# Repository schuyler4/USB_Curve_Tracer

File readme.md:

<h2> USB Curve Tracer </h2>
This is my attempt at making a curve tracer.  
Instead of implementing a display, data is piped to an external computer where it is plotted using Python. It is also controlled using a command line interface on the external computer. 

<h3> Revision 3 Specs </h3>
<ul>
<li>12V External Power Supply</li>
<li>Maximum Positive Sweep Voltage: 4V</li>
<li>Minimum Negative Sweep Voltage: -3.9V</li>
<li>Full Sweep Time: 15.4s</li>
</ul>

<h3> Limitations </h3>
<ul>
<li>The curve tracer does not use sinusoidal waveforms for measurement; measuring reactive components 
(Capacitors and Inductors) probably will not work. </li>
<li>The curve tracer cannot be driven, so it cannot measure voltage sources.</li>
<li>The curve tracer does not include Kelvin connection functionality, so test lead resistance and 
contact resistance will be included in the measurement. </li>
<li> The curve tracer does not include any programmable gain stages. For this reason, you only get full
current/voltage measurement when using the full current/voltage range.</li>
</ul> 

<h3> Examples </h3>
<p>Below is an example 1N4148 diode sweep and a 2N3904 BJT sweep. Short of curve tracing with a different system and doing a comparison, there is not really a good way to verify if these are correct. However, the general shape of the curves does look right. There is clearly some offset error for the red trace of the 2N3904 sweep. </p>

<h3> Schematic </h3>

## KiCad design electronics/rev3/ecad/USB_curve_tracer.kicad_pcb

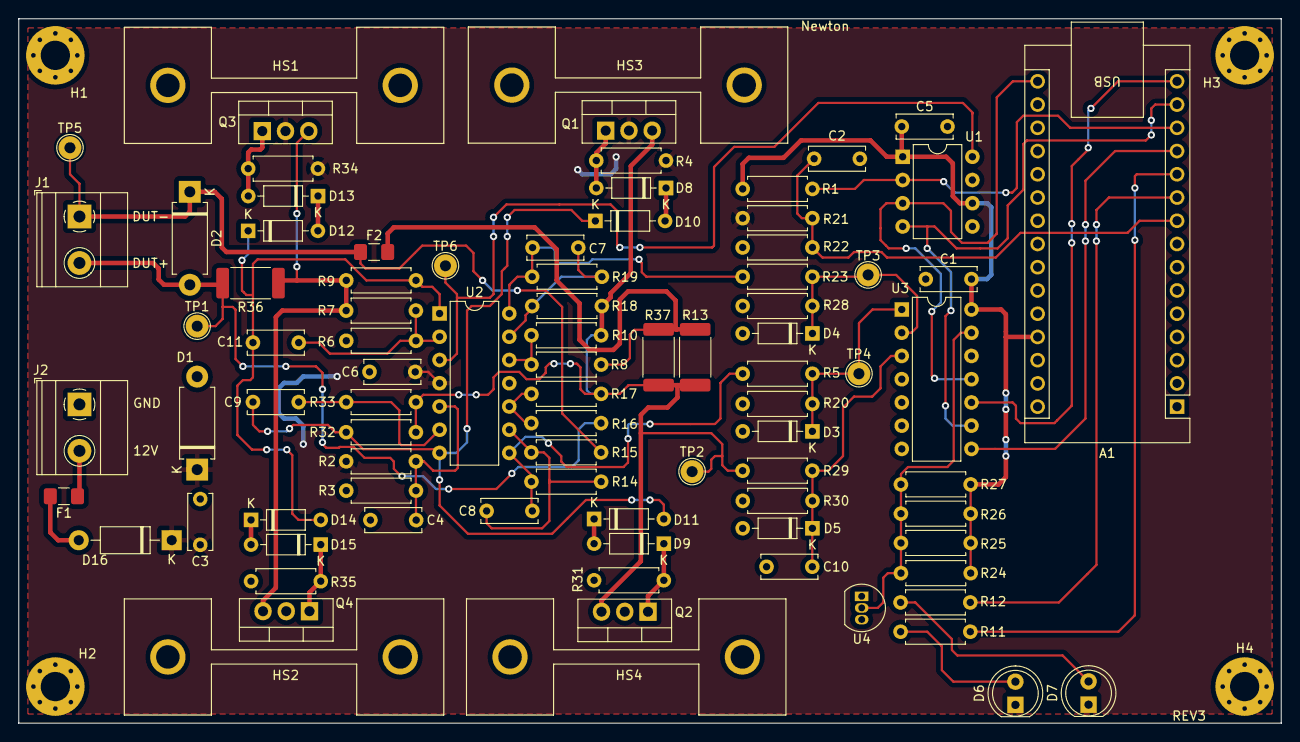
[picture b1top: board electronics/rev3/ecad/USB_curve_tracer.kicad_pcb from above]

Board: 2 copper layers, 138.0 x 77.0 mm, 91 parts (0 on the bottom side), 44 nets.

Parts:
A1: Arduino_Nano_v3.x; Arduino_Nano
C1, C2, C4, C5, C6, C10: 0.1uF; C_Disc_D6.0mm_W2.5mm_P5.00mm
C3: 10uF; C_Disc_D6.0mm_W2.5mm_P5.00mm
C7, C8: 10nF; C_Disc_D6.0mm_W2.5mm_P5.00mm
C9, C11: 100pF; C_Disc_D6.0mm_W2.5mm_P5.00mm
D1: SA13A; D_DO-15_P10.16mm_Horizontal
D2: SA13CA; D_DO-15_P10.16mm_Horizontal
D3, D4, D5: BZX79-C2V4; D_DO-35_SOD27_P7.62mm_Horizontal
D6: WP7113SGD; LED_D5.0mm
D7: WP7113ID; LED_D5.0mm
D8, D9, D10, D11, D12, D13, D14, D15: 1N4148; D_DO-35_SOD27_P7.62mm_Horizontal
D16: 1N5817; D_DO-41_SOD81_P10.16mm_Horizontal
F1: 3A; Fuse_1206_3216Metric_Pad1.42x1.75mm_HandSolder
F2: 1A; Fuse_1206_3216Metric_Pad1.42x1.75mm_HandSolder
H1, H2, H3, H4: M3; MountingHole_3.2mm_M3_Pad_Via
HS1, HS2, HS3, HS4: 13.40°C/W; HSINK_531002B02500G
J1: DUT Connector; TerminalBlock_Phoenix_MKDS-1,5-2-5.08_1x02_P5.08mm_Horizont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
J2: Power Input; TerminalBlock_Phoenix_MKDS-1,5-2-5.08_1x02_P5.08mm_Horizont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
Q1, Q3: TIP122; TO-220-3_Vertical
Q2, Q4: TIP127; TO-220-3_Vertical
R1, R2, R3, R6, R7, R22, R24, R25, R26, R27, R33: 10k; R_Axial_DIN0207_L6.3mm_D2.5mm_P7.62mm_Horizontal
R4, R31, R34, R35: 4.7k; R_Axial_DIN0207_L6.3mm_D2.5mm_P7.62mm_Horizontal
R5, R23, R29: 3.83k+/-0.1%; R_Axial_DIN0207_L6.3mm_D2.5mm_P7.62mm_Horizontal
R8, R18, R20, R28: 1k+/-0.1%; R_Axial_DIN0207_L6.3mm_D2.5mm_P7.62mm_Horizontal
R9, R30, R32: 1k; R_Axial_DIN0207_L6.3mm_D2.5mm_P7.62mm_Horizontal
R10, R19: 11.8k+/-0.1%; R_Axial_DIN0207_L6.3mm_D2.5mm_P7.62mm_Horizontal
R11, R12: 619; R_Axial_DIN0207_L6.3mm_D2.5mm_P7.62mm_Horizontal
R13, R37: 1+/-1%; R_2512_6332Metric_Pad1.40x3.35mm_HandSolder
R14, R15, R16, R17: 10k+/-0.1%; R_Axial_DIN0207_L6.3mm_D2.5mm_P7.62mm_Horizontal
R21: 14k; R_Axial_DIN0207_L6.3mm_D2.5mm_P7.62mm_Horizontal
R36: 1.5; R_2512_6332Metric_Pad1.40x3.35mm_HandSolder
TP1, TP2, TP3, TP4, TP5, TP6: 4952; TestPoint_THTPad_D2.5mm_Drill1.2mm
U1: MCP4911; DIP-8_W7.62mm
U2: LMC6484A; DIP-14_W7.62mm
U3: MCP3204; DIP-14_W7.62mm
U4: LM385BZ-2.5; TO-92_Inline

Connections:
+5V: A1.27 (+5V), C1.1, C5.1, R1.1, R24.1, R25.1, R26.1, R27.1, U1.1 (Vdd), U1.6 (Vref), U3.14 (Vdd)
+12V: C3.1, C6.1, D1.1 (K), D16.1 (K), Q1.2 (C), Q3.2 (C), R2.1, R4.1, R21.1, R34.1, U2.4 (V+)
/IV_Variation/DUT_I: D4.1 (K), R23.2, R28.1, TP3.1, U3.2 (CH1)
/IV_Variation/DUT_V: D3.1 (K), R5.2, R20.1, TP4.1, U3.1 (CH0)
/IV_Variation/Sweep Voltage Buffer/Sweep_Amplified: Q3.3 (E), Q4.3 (E), R7.2, R9.2, R36.1
/IV_Variation/Sweep_Input: TP6.1, U1.8 (Vout), U2.3 (+)
/IV_Variation/Vmiddle: C10.1, D5.1 (K), R29.2, R30.1, U3.3 (CH2)
GND: A1.4 (GND), A1.29 (GND), C1.2, C2.2, C3.2, C4.2, C5.2, C6.2, C10.2, D1.2 (A), D3.2 (A), D4.2 (A), D5.2 (A), D6.1 (K), D7.1 (K), H1.1, H2.1, H3.1, H4.1, J2.1, Q2.2 (C), Q4.2 (C), R3.2, R6.2, R20.2, R22.2, R28.2, R30.2, R31.2, R35.2, U1.5 (~LDAC), U1.7 (Vss), U2.11 (V-), U3.7 (DGND), U3.12 (AGND), U4.3 (A)
unnamed: A1.9 (D6), C2.1, R21.2, R22.1
unnamed: A1.10 (D7), R12.2
unnamed: A1.11 (D8), R11.2
unnamed: A1.12 (D9), U3.8 (~CS/SHDN)
unnamed: A1.13 (D10), R1.2, U1.2 (~CS)
unnamed: A1.14 (D11), U1.4 (SDI), U3.9 (Din)
unnamed: A1.15 (D12), U3.10 (Dout)
unnamed: A1.16 (D13), U1.3 (SCK), U3.11 (CLK)
unnamed: C7.2, R19.2, R23.1, U2.14
unnamed: C8.2, R5.1, R14.2, U2.8
unnamed: D2.1 (A1), F2.1, J1.1, R15.1, TP5.1
unnamed: D2.2 (A2), J1.2, R16.1, R36.2, TP1.1
unnamed: D6.2 (A), R11.1
unnamed: D7.2 (A), R12.1
unnamed: D8.2 (A), Q1.1 (B), R4.2
unnamed: D9.1 (K), Q2.1 (B), R31.1
unnamed: D8.1 (K), D10.2 (A)
unnamed: C9.2, D10.1 (K), D11.2 (A), R32.1, U2.7
unnamed: D9.2 (A), D11.1 (K)
unnamed: D12.2 (A), D13.1 (K)
unnamed: C11.1, D12.1 (K), D14.2 (A), R9.1, U2.1
unnamed: D13.2 (A), Q3.1 (B), R34.2
unnamed: D14.1 (K), D15.2 (A)
unnamed: D15.1 (K), Q4.1 (B), R35.1
unnamed: D16.2 (A), F1.2
unnamed: F2.2, R8.1, R13.1, R37.1
unnamed: F1.1, J2.2
unnamed: C11.2, R6.1, R7.1, U2.2 (-)
unnamed: C4.1, R2.2, R3.1, U2.5 (+)
unnamed: C9.1, R33.1, U2.6 (-)
unnamed: R16.2, R17.1, U2.10 (+)
unnamed: C8.1, R14.1, R15.2, U2.9 (-)
unnamed: R8.2, R10.1, U2.12 (+)
unnamed: C7.1, R18.2, R19.1, U2.13 (-)
unnamed: R24.2, R25.2, R26.2, R27.2, U3.13 (Vref), U4.2 (K)
V/2: Q1.3 (E), Q2.3 (E), R10.2, R13.2, R17.2, R18.1, R29.1, R32.2, R33.2, R37.2, TP2.1

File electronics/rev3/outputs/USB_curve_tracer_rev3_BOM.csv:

Item,Qty,Reference(s),Value,Distributor Part #,Part #,Unit Price,Price
1,1,A1,Arduino_Nano_v3.x,1050-ABX00033-ND,ABX00033,14.91,14.91
2,6,"C1, C2, C4, C5, C6, C10",0.1uF,BC2665CT-ND,K104K10X7RF5UH5,0.23,1.38
3,1,C3,10uF,445-173437-1-ND,FG26X7R1E106KRT06,0.65,0.65
4,2,"C7, C8",10nF,BC2662CT-ND,K103K10X7RF5UH5,0.22,0.44
5,2,"C9, C11",100pF,56-K101J10C0GF5UH5CT-ND,K101J10C0GF5UH5,0.23,0.46
6,1,D1,SA13A,SA13A-E3/54GICT-ND,SA13A-E3/54,0.46,0.46
7,1,D2,SA13CA,SA13CACT-ND,SA13CA,0.49,0.49
8,3,"D3, D4, D5",BZX79-C2V4,1727-2115-1-ND,"BZX79-C2V4,113",0.16,0.48
9,1,D6,WP7113SGD,754-1735-ND,WP7113SGD,0.34,0.34
10,1,D7,WP7113ID,754-1264-ND,WP7113ID,0.1,0.1
11,8,"D8, D9, D10, D11, D12, D13, D14, D15",1N4148,1N4148FS-ND,1N4148,0.1,0.8
12,1,D16,1N5817,497-4547-1-ND,1N5817,0.44,0.44
13,1,F1,3A,507-1896-1-ND,0685T3000-01,0.32,0.32
14,1,F2,1A,507-1077-1-ND,C1Q 1,0.33,0.33
15,4,"HS1, HS2, HS3, HS4",13.40°C/W,HS351-ND,531002B02500G,1.55,6.2
16,1,J1,DUT Connector,102-6179-ND,TB004-508-02BE,0.71,0.71
17,1,J2,Power Input,102-6179-ND,TB004-508-02BE,0.71,0.71
18,2,"Q1, Q3",TIP122,TIP122GOS-ND,TIP122G,0.79,1.58
19,2,"Q2, Q4",TIP127,TIP127GOS-ND,TIP127G,1.37,2.74
20,11,"R1, R2, R3, R6, R7, R22, R24, R25, R26, R27, R33",10k,CF14JT10K0CT-ND,CF14JT10K0,0.1,1.1
21,4,"R4, R31, R34, R35",4.7k,CF14JT4K70CT-ND,CF14JT4K70,0.1,0.4
22,3,"R5, R23, R29",4.02k+/-0.1%,1712-YR1B4K02CT-ND,YR1B4K02,0.63,1.89
23,4,"R8, R18, R20, R28",1k+/-0.1%,A105942CT-ND,YR1B1K0CC,0.63,2.52
24,3,"R9, R30, R32",1k,13-MFR-25FRF52-1KCT-ND,MFR-25FRF52-1K,0.1,0.3
25,2,"R10, R19",11.8k+/-0.1%,1712-YR1B11K8CCCT-ND,YR1B11K8CC,0.63,1.26
26,2,"R11, R12",619,619XBK-ND,MFR-25FBF52-619R,0.1,0.2
27,2,"R13, R37",1+/-1%,RMCF2512FT1R00CT-ND,RMCF2512FT1R00,0.27,0.54
28,4,"R14, R15, R16, R17",10k+/-0.1%,A105970CT-ND,YR1B10KCC,0.63,2.52
29,1,R21,14k,14.0KXBK-ND,MFR-25FBF52-14K,0.1,0.1
30,1,R36,1.5,A121179CT-ND,35221R5JT,1.22,1.22
31,6,"TP1, TP2, TP3, TP4, TP5, TP6",4952,36-4952-ND,4952,0.26,1.56
32,1,U1,MCP4911,MCP4911-E/P-ND,MCP4911-E/P,1.97,1.97
33,1,U2,LMC6484A,LMC6484IN/NOPB-ND,LMC6484IN/NOPB,2.83,2.83
34,1,U3,MCP3204,MCP3204-CI/P-ND,MCP3204-CI/P,4.52,4.52
35,1,U4,LM385BZ-2.5,LM385BZ-2.5GOS-ND,LM385BZ-2.5G,0.78,0.78
,,,,,,,57.25

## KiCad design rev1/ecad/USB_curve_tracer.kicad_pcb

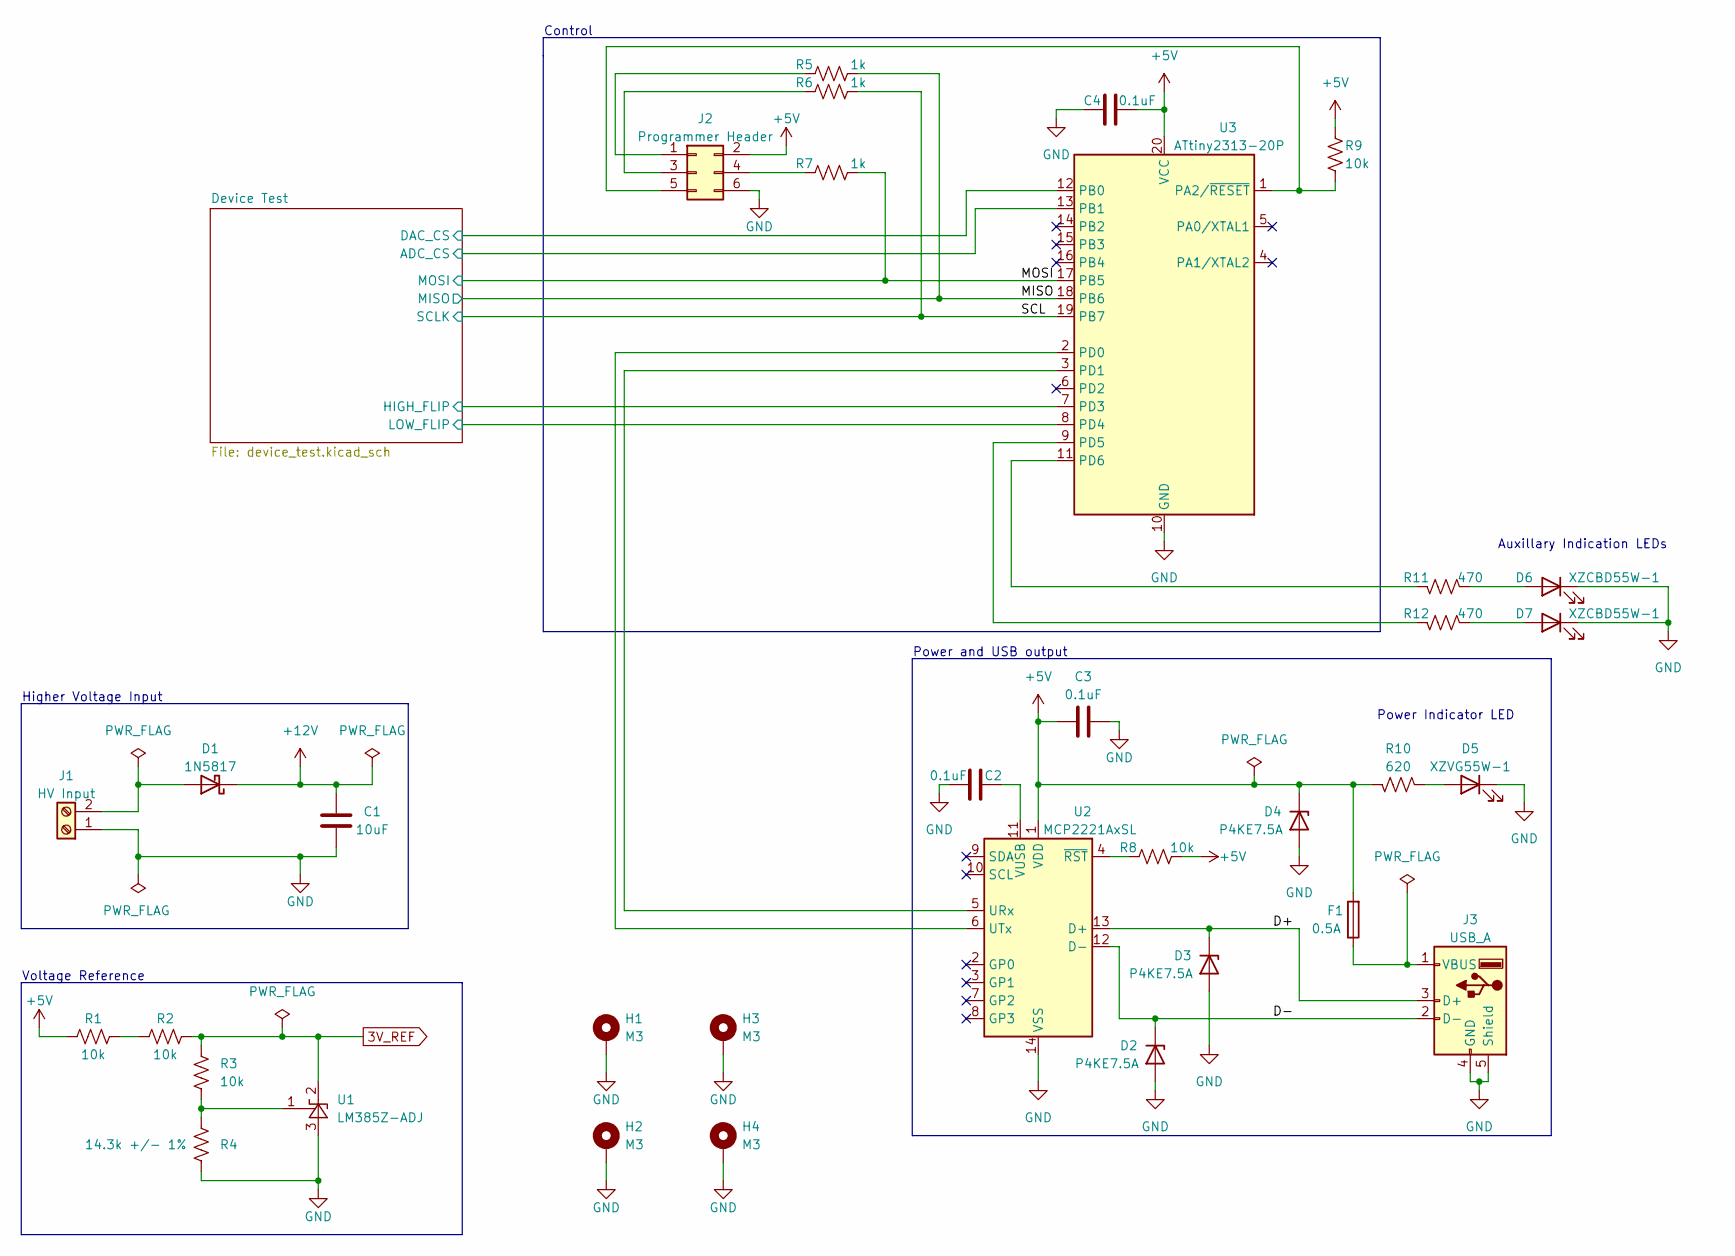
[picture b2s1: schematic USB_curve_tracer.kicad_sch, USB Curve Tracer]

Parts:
C1: 10uF; C_Disc_D6.0mm_W2.5mm_P5.00mm
C2, C3, C4: 0.1uF; C_Disc_D6.0mm_W2.5mm_P5.00mm
D1: 1N5817; D_DO-41_SOD81_P10.16mm_Horizontal
D2, D3, D4: P4KE7.5A; D_DO-41_SOD81_P7.62mm_Horizontal
D5: XZVG55W-1; LED_1206_3216Metric_Pad1.42x1.75mm_HandSolder
D6, D7: XZCBD55W-1; LED_1206_3216Metric_Pad1.42x1.75mm_HandSolder
F1: 0.5A; Fuse_1206_3216Metric_Pad1.42x1.75mm_HandSolder
H1, H2, H3, H4: M3; MountingHole_3.2mm_M3_Pad_Via
J1: HV Input; TerminalBlock_Phoenix_MKDS-1,5-2-5.08_1x02_P5.08mm_Horizont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
J2: Programmer Header; PinSocket_2x03_P2.54mm_Vertical
J3: USB_A; USB_B_OST_USB-B1HSxx_Horizontal
R1, R2, R3, R8, R9: 10k; R_Axial_DIN0207_L6.3mm_D2.5mm_P7.62mm_Horizontal
R4: 14.3k +/- 1%; R_Axial_DIN0207_L6.3mm_D2.5mm_P7.62mm_Horizontal
R5, R6, R7: 1k; R_Axial_DIN0207_L6.3mm_D2.5mm_P7.62mm_Horizontal
R10: 620; R_Axial_DIN0207_L6.3mm_D2.5mm_P7.62mm_Horizontal
R11, R12: 470; R_Axial_DIN0207_L6.3mm_D2.5mm_P7.62mm_Horizontal
U1: LM385Z-ADJ; TO-92_Inline
U2: MCP2221AxSL; SOIC-14_3.9x8.7mm_P1.27mm
U3: ATtiny2313-20P; DIP-20_W7.62mm

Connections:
3V_REF: R2.2, R3.1, U1.2 (K); also elsewhere on the board
+5V: C3.2, C4.2, D4.1 (K), F1.2, J2.2, R1.1, R8.2, R9.1, R10.2, U2.1 (VDD), U3.20 (VCC); also elsewhere on the board
+12V: C1.2, D1.1 (K); also elsewhere on the board
/D+: D3.1 (K), J3.3 (D+), U2.13 (D+)
/D-: D2.1 (K), J3.2 (D-), U2.12 (D-)
/Device Test/ADC_CS: U3.13 (PB1); also elsewhere on the board
/Device Test/DAC_CS: U3.12 (PB0); also elsewhere on the board
/Device Test/HIGH_FLIP: U3.7 (PD3); also elsewhere on the board
/Device Test/LOW_FLIP: U3.8 (PD4); also elsewhere on the board
/MISO: R5.2, U3.18 (PB6); also elsewhere on the board
/MOSI: R7.2, U3.17 (PB5); also elsewhere on the board
/SCL: R6.2, U3.19 (PB7); also elsewhere on the board
GND: C1.1, C2.2, C3.1, C4.1, D2.2 (A), D3.2 (A), D4.2 (A), D5.1 (K), D6.1 (K), D7.1 (K), H1.1, H2.1, H3.1, H4.1, J1.1, J2.6, J3.4 (GND), J3.5 (Shield), R4.2, U1.3 (A), U2.14 (VSS), U3.10 (GND); also elsewhere on the board
unnamed: C2.1, U2.11 (VUSB)
unnamed: D1.2 (A), J1.2
unnamed: D5.2 (A), R10.1
unnamed: D6.2 (A), R11.1
unnamed: D7.2 (A), R12.1
unnamed: F1.1, J3.1 (VBUS)
unnamed: J2.1, R5.1
unnamed: J2.3, R6.1
unnamed: J2.4, R7.1
unnamed: J2.5, R9.2, U3.1 (PA2/~RESET)
unnamed: R1.2, R2.1
unnamed: R3.2, R4.1, U1.1 (FB)
unnamed: R8.1, U2.4 (~RST)
unnamed: R11.2, U3.11 (PD6)
unnamed: R12.2, U3.9 (PD5)
unnamed: U2.5 (URx), U3.3 (PD1)
unnamed: U2.6 (UTx), U3.2 (PD0)

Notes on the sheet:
Power Indicator LED
Voltage Reference
Control
Power and USB output
Higher Voltage Input
Auxillary Indication LEDs

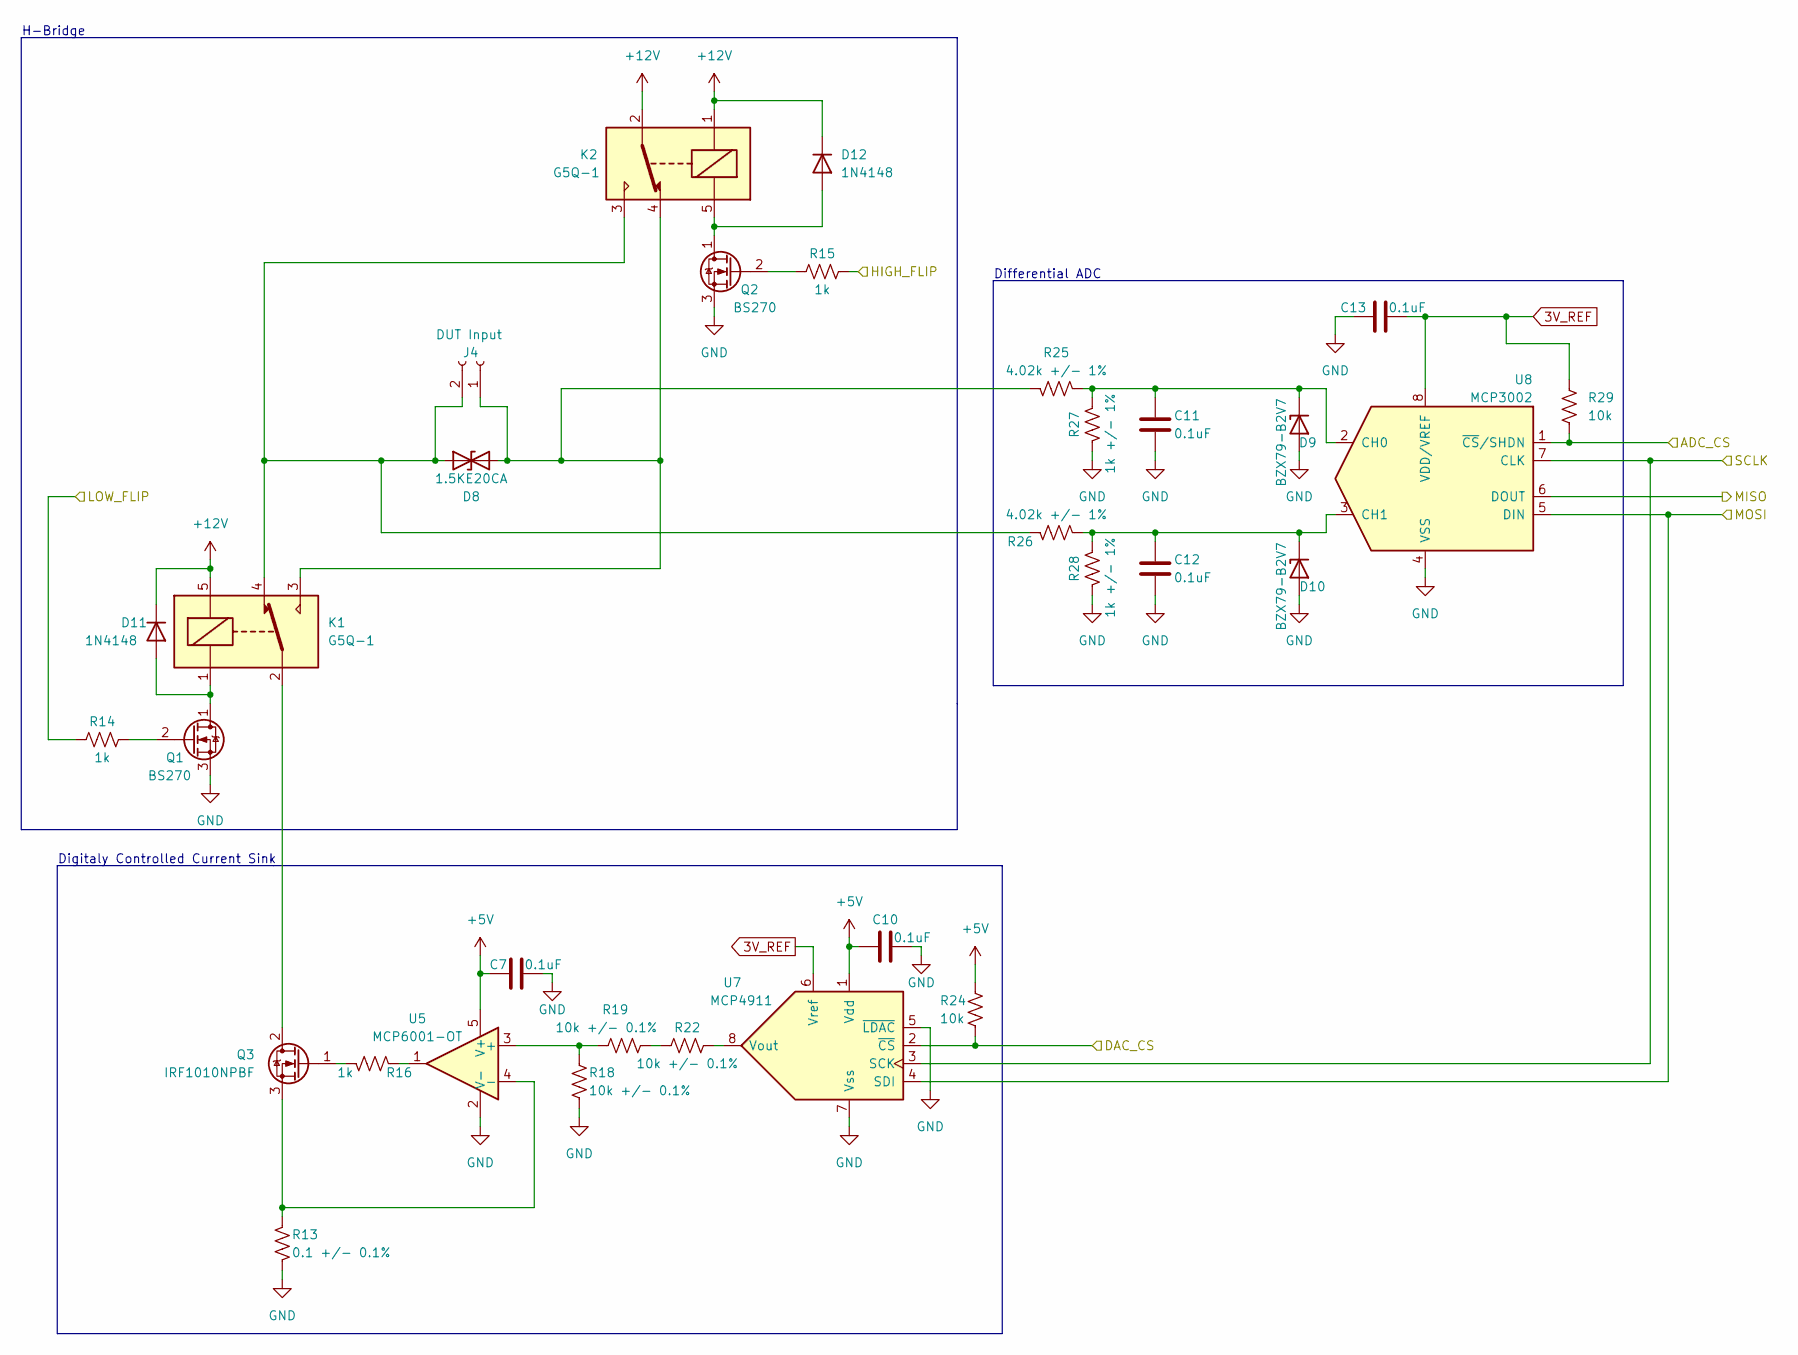
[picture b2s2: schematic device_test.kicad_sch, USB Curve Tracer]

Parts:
C7, C10, C11, C12, C13: 0.1uF; C_Disc_D6.0mm_W2.5mm_P5.00mm
D8: 1.5KE20CA; D_SMA_Handsoldering
D9, D10: BZX79-B2V7; D_DO-41_SOD81_P7.62mm_Horizontal
D11, D12: 1N4148; D_DO-35_SOD27_P7.62mm_Horizontal
J4: DUT Input; PinSocket_1x02_P2.54mm_Vertical
K1, K2: G5Q-1; Relay_SPDT_Omron-G5Q-1
Q1, Q2: BS270; TO-92_Inline
Q3: IRF1010NPBF; TO-220-3_Vertical
R13: 0.1 +/- 0.1%; R_Axial_DIN0207_L6.3mm_D2.5mm_P7.62mm_Horizontal
R14, R15, R16: 1k; R_Axial_DIN0207_L6.3mm_D2.5mm_P7.62mm_Horizontal
R18, R19, R22: 10k +/- 0.1%; R_Axial_DIN0207_L6.3mm_D2.5mm_P7.62mm_Horizontal
R24, R29: 10k; R_Axial_DIN0207_L6.3mm_D2.5mm_P7.62mm_Horizontal
R25, R26: 4.02k +/- 1%; R_Axial_DIN0207_L6.3mm_D2.5mm_P7.62mm_Horizontal
R27, R28: 1k +/- 1%; R_Axial_DIN0207_L6.3mm_D2.5mm_P7.62mm_Horizontal
U5: MCP6001-OT; SOT-23-5
U7: MCP4911; DIP-8_W7.62mm
U8: MCP3002; DIP-8_W7.62mm

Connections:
3V_REF: C13.1, R29.1, U7.6 (Vref), U8.8 (VDD/VREF); also elsewhere on the board
+5V: C7.2, C10.2, R24.1, U5.5 (V+), U7.1 (Vdd); also elsewhere on the board
+12V: D11.1 (K), D12.1 (K), K1.5, K2.1, K2.2; also elsewhere on the board
/Device Test/ADC_CS: R29.2, U8.1 (~CS/SHDN); also elsewhere on the board
/Device Test/DAC_CS: R24.2, U7.2 (~CS); also elsewhere on the board
/Device Test/HIGH_FLIP: R15.2; also elsewhere on the board
/Device Test/LOW_FLIP: R14.1; also elsewhere on the board
/MISO: U8.6 (DOUT); also elsewhere on the board
/MOSI: U7.4 (SDI), U8.5 (DIN); also elsewhere on the board
/SCL: U7.3 (SCK), U8.7 (CLK); also elsewhere on the board
GND: C7.1, C10.1, C11.2, C12.2, C13.2, D9.2 (A), D10.2 (A), Q1.3 (S), Q2.3 (S), R13.2, R18.2, R27.1, R28.1, U5.2 (V-), U7.5 (~LDAC), U7.7 (Vss), U8.4 (VSS); also elsewhere on the board
unnamed: C11.1, D9.1 (K), R25.1, R27.2, U8.2 (CH0)
unnamed: C12.1, D10.1 (K), R26.1, R28.2, U8.3 (CH1)
unnamed: D8.1 (A1), J4.2, K1.4, K2.3, R26.2
unnamed: D8.2 (A2), J4.1, K1.3, K2.4, R25.2
unnamed: D11.2 (A), K1.1, Q1.1 (D)
unnamed: D12.2 (A), K2.5, Q2.1 (D)
unnamed: K1.2, Q3.2 (D)
unnamed: Q2.2 (G), R15.1
unnamed: Q3.3 (S), R13.1, U5.4 (-)
unnamed: Q1.2 (G), R14.2
unnamed: R16.1, U5.1
unnamed: Q3.1 (G), R16.2
unnamed: R18.1, R19.1, U5.3 (+)
unnamed: R19.2, R22.1
unnamed: R22.2, U7.8 (Vout)

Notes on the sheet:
Digitaly Controlled Current Sink
Differential ADC
H-Bridge

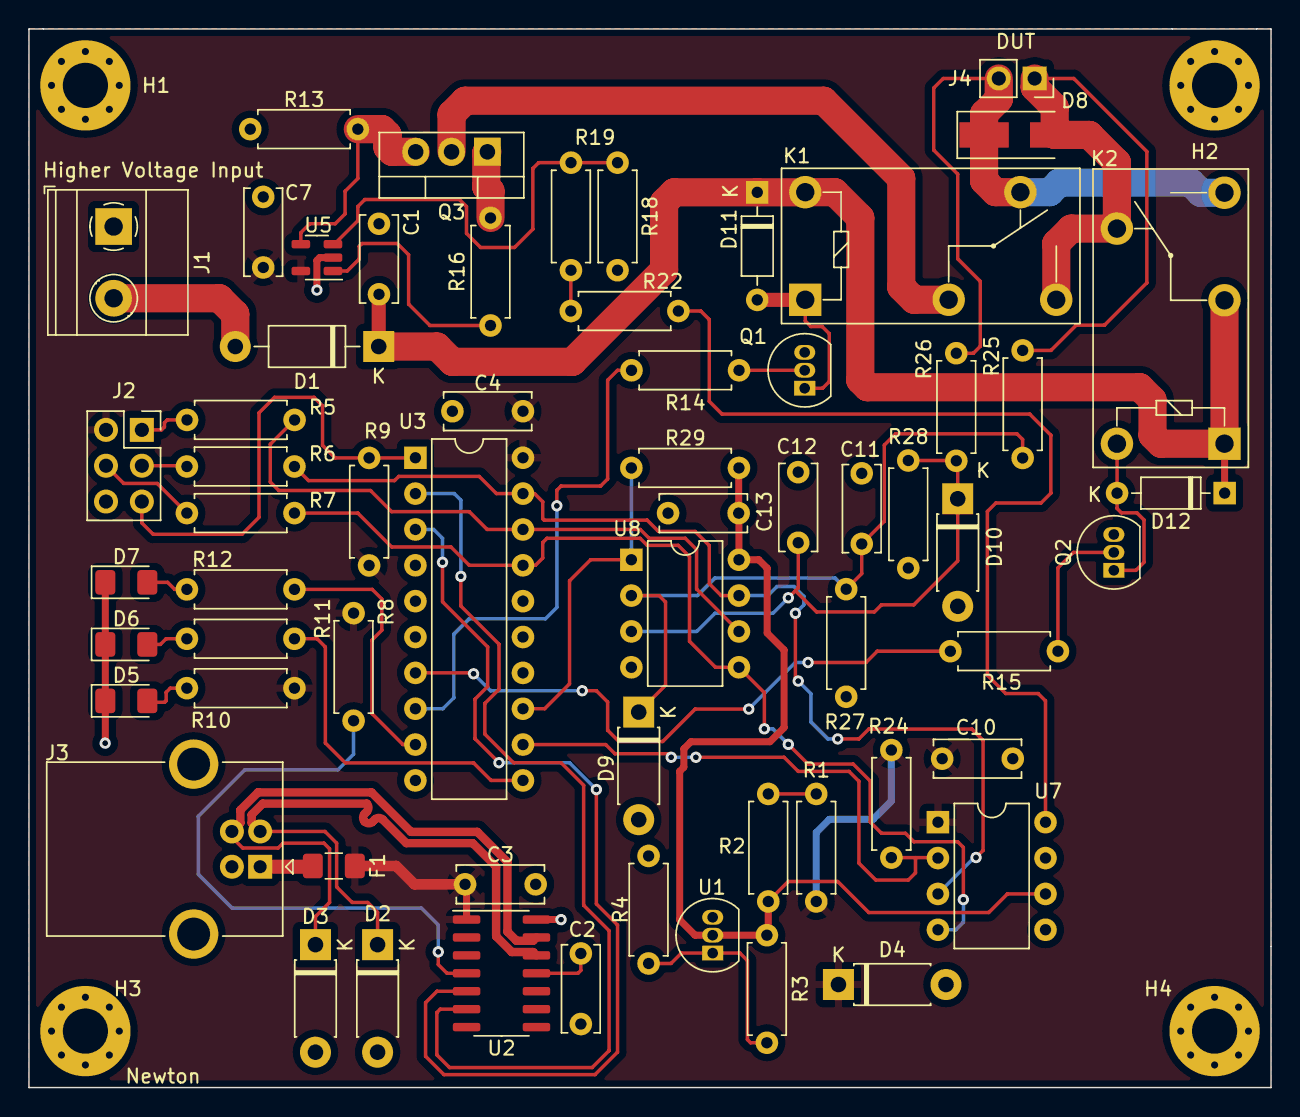
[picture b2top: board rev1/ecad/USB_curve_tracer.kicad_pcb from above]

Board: 2 copper layers, 88.0 x 75.0 mm, 66 parts (0 on the bottom side), 45 nets.

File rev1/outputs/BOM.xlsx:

Item | Qty | Reference(s) | Value | Digikey Part # | Unit Price | Price | Notes
1 | 1 | C1 | 10uF | 445-181259-ND | 0.56000000000000005 | 0.56000000000000005
2 | 8 | C2, C3, C4, C7, C10, C11, C12, C13 | 0.1uF | 399-4329-ND | 0.24 | 1.92
3 | 1 | D1 | 1N5817 | 497-4547-1-ND | 0.42 | 0.42
4 | 3 | D2, D3, D4 | P4KE7.5A | P4KE7.5ACT-ND | 0.52 | 1.56
5 | 1 | D5 | XZVG55W-1 | 1497-1217-1-ND | 0.39 | 0.39
6 | 2 | D6, D7 | XZCBD55W-1 | 1497-1119-1-ND | 0.49 | 0.98
7 | 1 | D8 | 1.5KE20CA | 1.5KE20CALFCT-ND | 0.68 | 0.68
8 | 2 | D9, D10 | BZX79-B2V7 | 1727-4667-1-ND | 0.24 | 0.48
9 | 2 | D11, D12 | 1N4148 | 1N4148FS-ND | 0.1 | 0.2
10 | 1 | F1 | 0.5A | 507-1886-1-ND | 0.24 | 0.24
11 | 1 | J1 | HV Input | 102-6203-ND | 0.85 | 0.85
12 | 1 | J2 | Programmer Header | 609-3396-ND | 1.22 | 1.22
13 | 1 | J3 | USB_A | ED2983-ND | 0.61 | 0.61
14 | 1 | J4 | DUT Input | ED7364-02-ND | 0.51 | 0.51
15 | 2 | K1, K2 | G5Q-1 | Z219-ND | 1.63 | 3.26
16 | 2 | Q1, Q2 | BS270 | BS270FS-ND | 0.49 | 0.98
17 | 1 | Q3 | IRF1010NPBF | IRF1010NPBF-ND | 1.81 | 1.81
18 | 7 | R1, R2, R3, R8, R9, R24, R29 | 10k | 13-CFR-25JT-52-10KCT-ND | 0.1 | 0.70000000000000007
19 | 1 | R4 | 14.3k | RNF14FTD14K3CT-ND | 0.1 | 0.1
20 | 6 | R5, R6, R7, R14, R15, R16 | 1k | RNF14FTD14K3CT-ND | 0.1 | 0.60000000000000009
21 | 1 | R10 | 620 | 620QBK-ND | 0.1 | 0.1
22 | 2 | R11, R12 | 470 | 470QBK-ND | 0.1 | 0.2
23 | 1 | R13 | 0.1 +/- 1% | WHBR10FETR-ND | 1.34 | 1.34
24 | 3 | R18, R19, R22 | 10k +/- 0.1% | 10KADCT-ND | 0.71 | 2.13
25 | 2 | R25, R26 | 2.34k +/- 1% | 4.02KXBK-ND | 0.1 | 0.2
26 | 2 | R27, R28 | 1k +/- 1% | PPC1.00KYCT-ND | 0.13 | 0.26
27 | 1 | U1 | LM385Z-ADJ | LM385Z/NOPB-ND | 1.25 | 1.25
28 | 1 | U2 | MCP2221AxSL | MCP2221-I/SL-ND | 2.9 | 2.9
29 | 1 | U3 | ATtiny2313-20P | N/A | 1.71 | 1.71 | Order from Arrow Electronics
30 | 1 | U5 | MCP6001-OT | 150-MCP6001T-E/OTVAOCT-ND | 0.31 | 0.31
31 | 1 | U7 | MCP4911 | MCP4911-E/P-ND | 1.98 | 1.98
32 | 1 | U8 | MCP3002 | MCP3002-I/P-ND | 2.58 | 2.58
total: |  |  |  |  |  | 33.03

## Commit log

2023-08-03 solid front end
2023-08-04 schematic work
2023-08-08 restructuring and layout
2023-08-12 layout
2023-08-15 removed ignored files
2023-08-27 created firmware baseline
2023-08-27 good start
2023-08-27 starting firmware
2023-08-28 DAC output voltage
2023-08-28 DAC and ADC
2023-08-29 Working ADC
2023-09-11 Linear Output
2023-09-13 proper ADC implementation
2023-09-13 DAC driver
2023-09-15 proper ramp and ADC
2023-09-15 stuff
2023-09-16 restructuring
2023-09-16 zener plot
2023-09-16 examples
2023-09-16 C interface
2023-09-16 start of PC interface
2023-09-18 reliable transmission
2023-09-23 preliminary box
2023-09-24 resistor testing
2023-09-24 readme
2023-09-25 added device picture
2023-09-25 removed mechanical
2023-09-27 REV3 start
2023-10-01 REV3 schematic
2023-10-06 Layout work
2023-10-18 start direction modes
2023-10-19 directional modes
2023-10-21 power disconnected
2023-10-22 something
2023-10-22 value changes
2023-11-02 added tolerance
2023-11-03 ratiometeric zero
2023-11-03 some traces on rev3
2023-11-04 some more rev3 traces and some problems
2023-11-05 REV3 testing
2023-11-05 start of current limiting
2023-11-05 removed zener diodes
2023-11-08 TIP122G test
2023-11-10 changed crossover resistor to 330
2023-11-10 LMC6484 REV3 test
2023-11-12 debug and misc
2023-11-17 added requirements
2023-11-18 more current limit work
2023-11-18 created examples directory
2023-11-18 fixed readme
2023-11-18 fixed readme again
2023-11-21 mechanical stuff
2023-11-28 working current limit
2023-11-28 new examples
2023-11-28 redword
2023-11-29 changed picture
2023-12-10 comparison test
2023-12-13 rev3 resistor test final
2023-12-15 attempy at scope comparison
2023-12-17 scope comparison
2023-12-23 Revert "scope comparison"
    This reverts commit d555587def78571ea5c9663f421cd88214450a50.
2023-12-24 mosfet sweep
2024-01-14 started step average
2024-01-14 Revert "started step average"
    This reverts commit faad6ccbaa3a507dd0bd96a70cac3c427b262546.
2024-01-15 ughh
2024-01-15 add software/bin to .gitignore
2024-01-16 step averaging algorithm
2024-01-16 typo
2024-03-11 added schematic to readme
2024-03-11 clean up
